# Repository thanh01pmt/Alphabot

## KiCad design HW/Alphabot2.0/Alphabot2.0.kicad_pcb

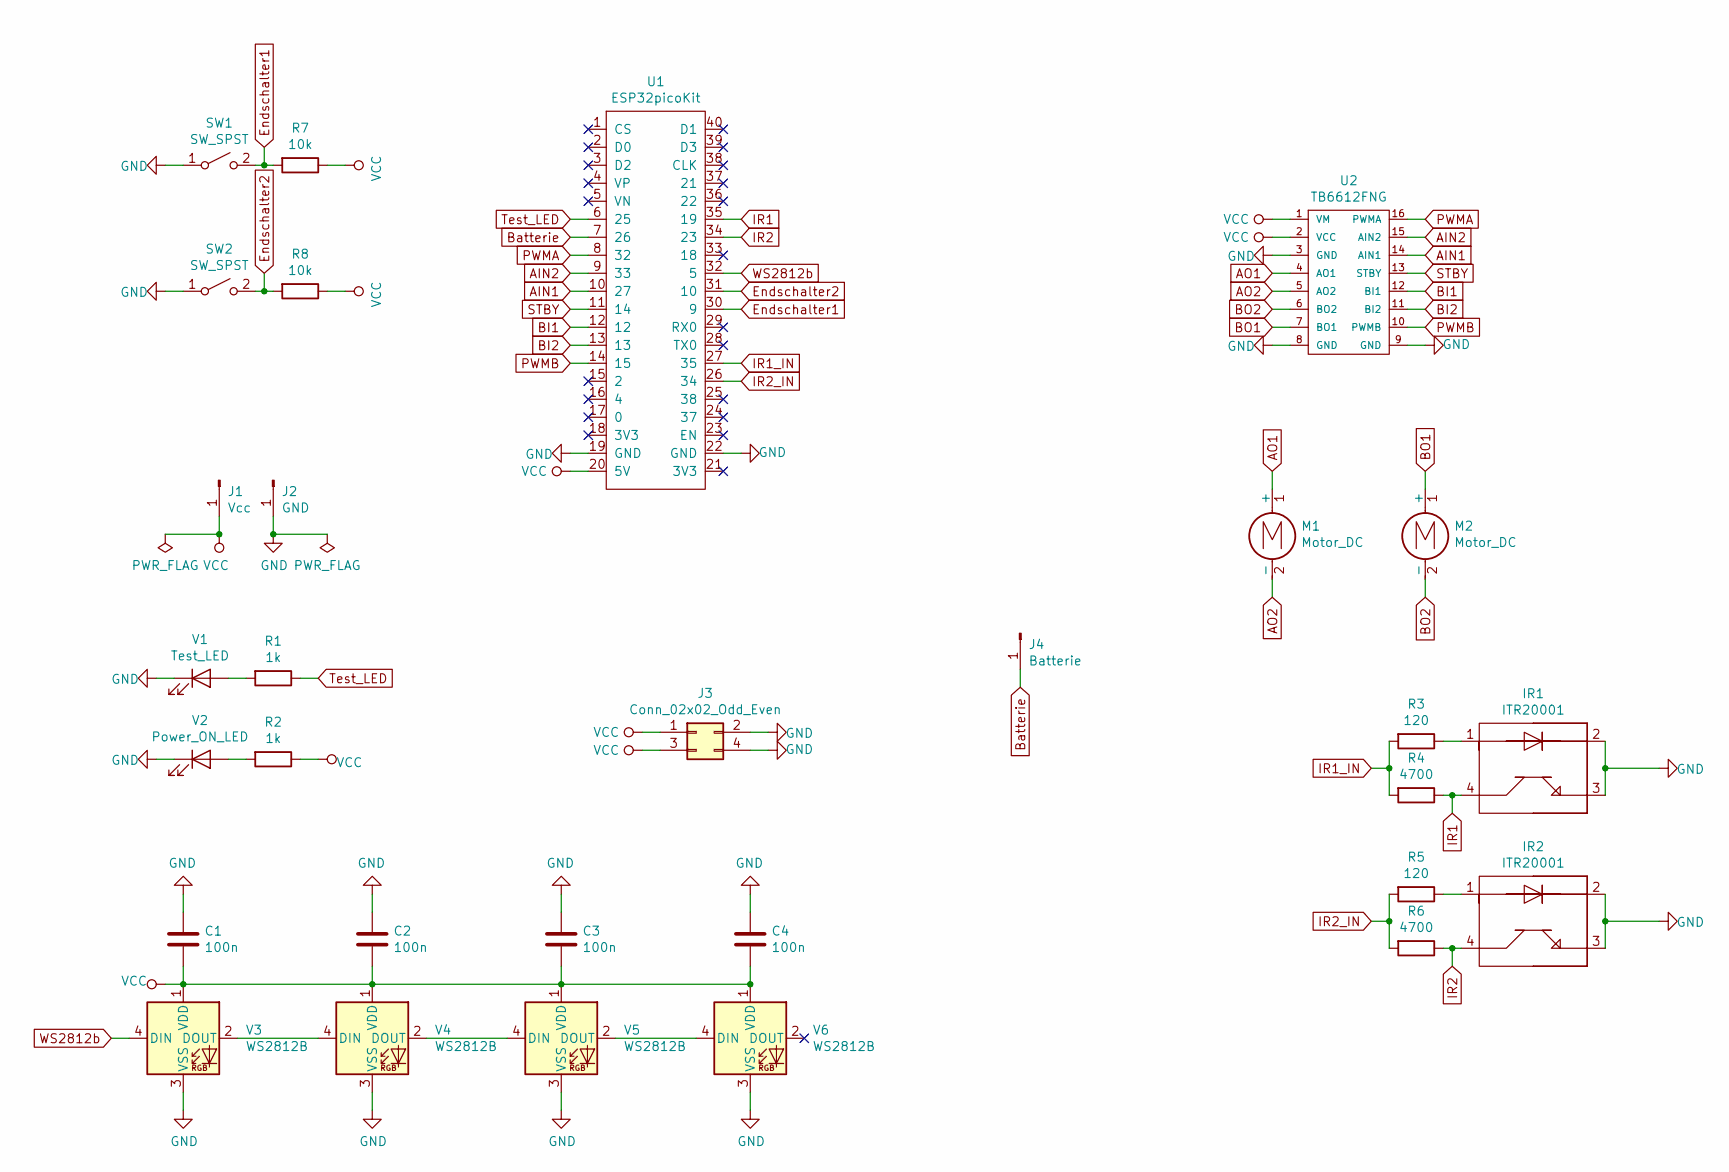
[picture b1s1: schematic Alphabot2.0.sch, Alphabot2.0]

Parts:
C1, C2, C3, C4: 100n; C_0805_2012Metric_Pad1.15x1.40mm_HandSolder
IR1, IR2: ITR20001; ITR20001-T
J1: Vcc; PinHeader_1x01_P2.54mm_Vertical
J2: GND; PinHeader_1x01_P2.54mm_Vertical
J3: Conn_02x02_Odd_Even; PinHeader_2x02_P2.54mm_Vertical_SMD
J4: Batterie; PinHeader_1x01_P2.54mm_Vertical
M1, M2: Motor_DC; N20_DC_Motor_mit_Halterung
R1, R2: 1k; R_0805_2012Metric_Pad1.15x1.40mm_HandSolder
R3, R5: 120; R_0805_2012Metric_Pad1.15x1.40mm_HandSolder
R4, R6: 4700; R_0805_2012Metric_Pad1.15x1.40mm_HandSolder
R7, R8: 10k; R_0805_2012Metric_Pad1.15x1.40mm_HandSolder
SW1, SW2: SW_SPST; Endschalter
U1: ESP32picoKit; ESP32_Pico_Kit
U2: TB6612FNG
V1: Test_LED; LED_0805_2012Metric_Pad1.15x1.40mm_HandSolder
V2: Power_ON_LED; LED_0805_2012Metric_Pad1.15x1.40mm_HandSolder
V3, V4, V5, V6: WS2812B; LED_WS2812B_PLCC4_5.0x5.0mm_P3.2mm

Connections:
AIN1: U1.10 (27), U2.14 (AIN1)
AIN2: U1.9 (33), U2.15 (AIN2)
AO1: M1.1 (+), U2.4 (AO1)
AO2: M1.2 (-), U2.5 (AO2)
BI1: U1.12, U2.12 (BI1)
BI2: U1.13, U2.11 (BI2)
BO1: M2.1 (+), U2.7 (BO1)
BO2: M2.2 (-), U2.6 (BO2)
Batterie: J4.1, U1.7 (26)
Endschalter1: R7.2, SW1.2 (B), U1.30 (9)
Endschalter2: R8.2, SW2.2 (B), U1.31 (10)
GND: C1.1, C2.1, C3.1, C4.1, IR1.2, IR1.3, IR2.2, IR2.3, J2.1, J3.2, J3.4, SW1.1 (A), SW2.1 (A), U1.19 (GND), U1.22 (GND), U2.3 (GND), U2.8 (GND), U2.9 (GND), V1.1 (K), V2.1 (K), V3.3 (VSS), V4.3 (VSS), V5.3 (VSS), V6.3 (VSS)
IR1: IR1.4, R4.1, U1.35 (19)
IR1_IN: R3.2, R4.2, U1.27 (35)
IR2: IR2.4, R6.1, U1.34 (23)
IR2_IN: R5.2, R6.2, U1.26 (34)
unnamed: IR1.1, R3.1
unnamed: IR2.1, R5.1
unnamed: R1.2, V1.2 (A)
unnamed: R2.2, V2.2 (A)
unnamed: V3.2 (DOUT), V4.4 (DIN)
unnamed: V4.2 (DOUT), V5.4 (DIN)
unnamed: V5.2 (DOUT), V6.4 (DIN)
PWMA: U1.8 (32), U2.16 (PWMA)
PWMB: U1.14 (15), U2.10 (PWMB)
STBY: U1.11 (14), U2.13 (STBY)
Test_LED: R1.1, U1.6 (25)
VCC: C1.2, C2.2, C3.2, C4.2, J1.1, J3.1, J3.3, R2.1, R7.1, R8.1, U1.20 (5V), U2.1 (VM), U2.2 (VCC), V3.1 (VDD), V4.1 (VDD), V5.1 (VDD), V6.1 (VDD)
WS2812b: U1.32 (5), V3.4 (DIN)

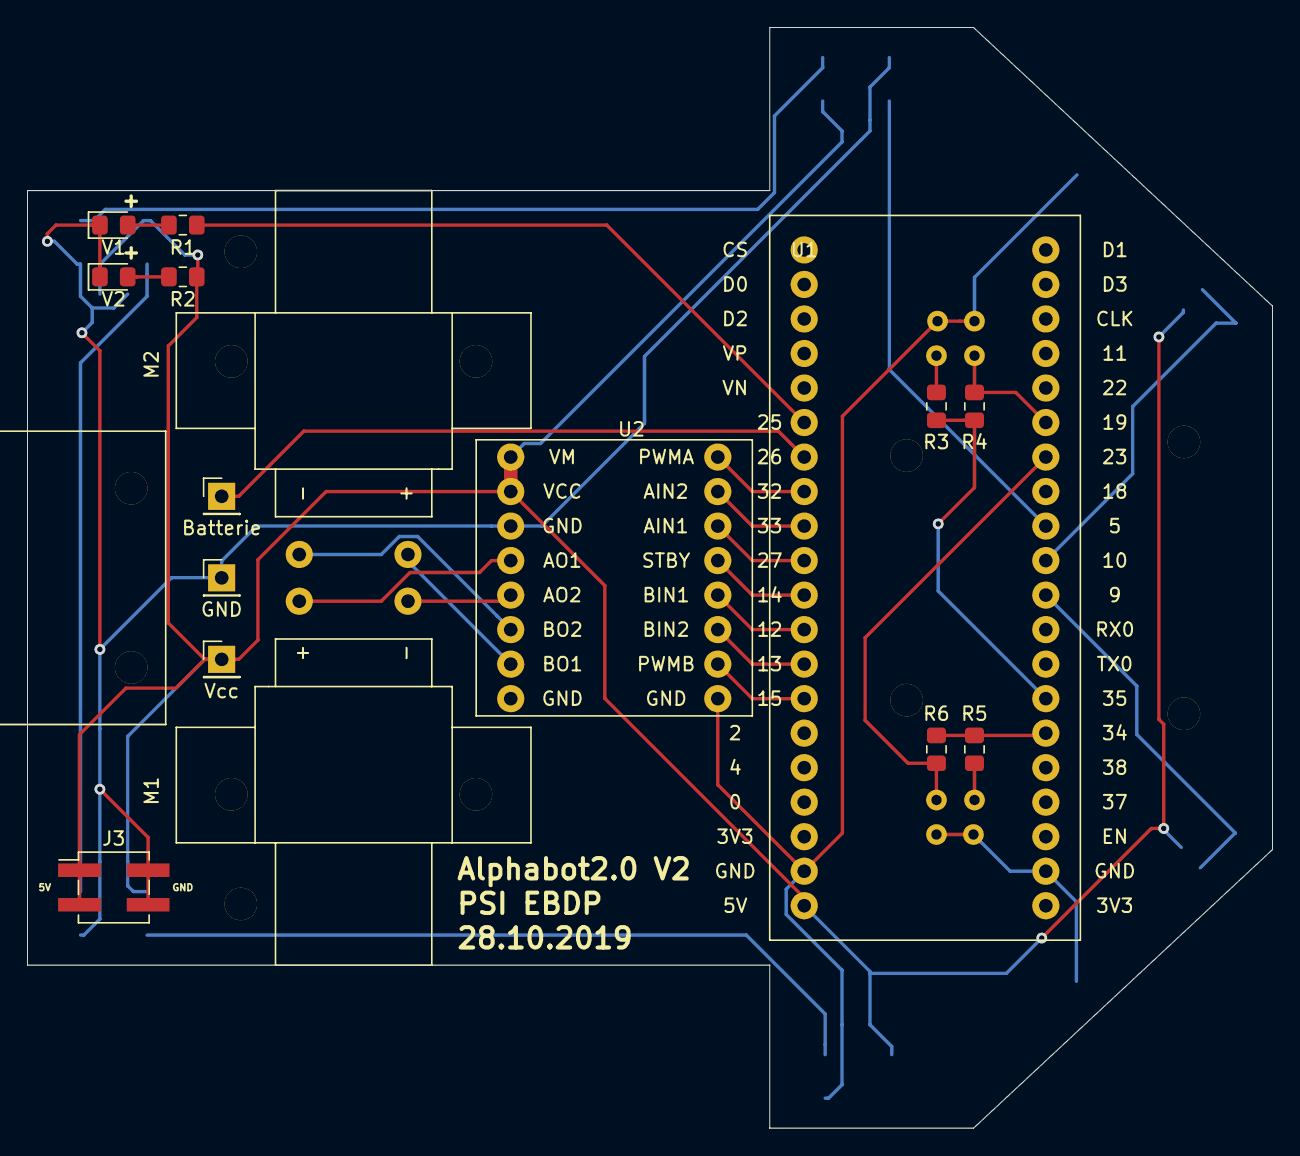
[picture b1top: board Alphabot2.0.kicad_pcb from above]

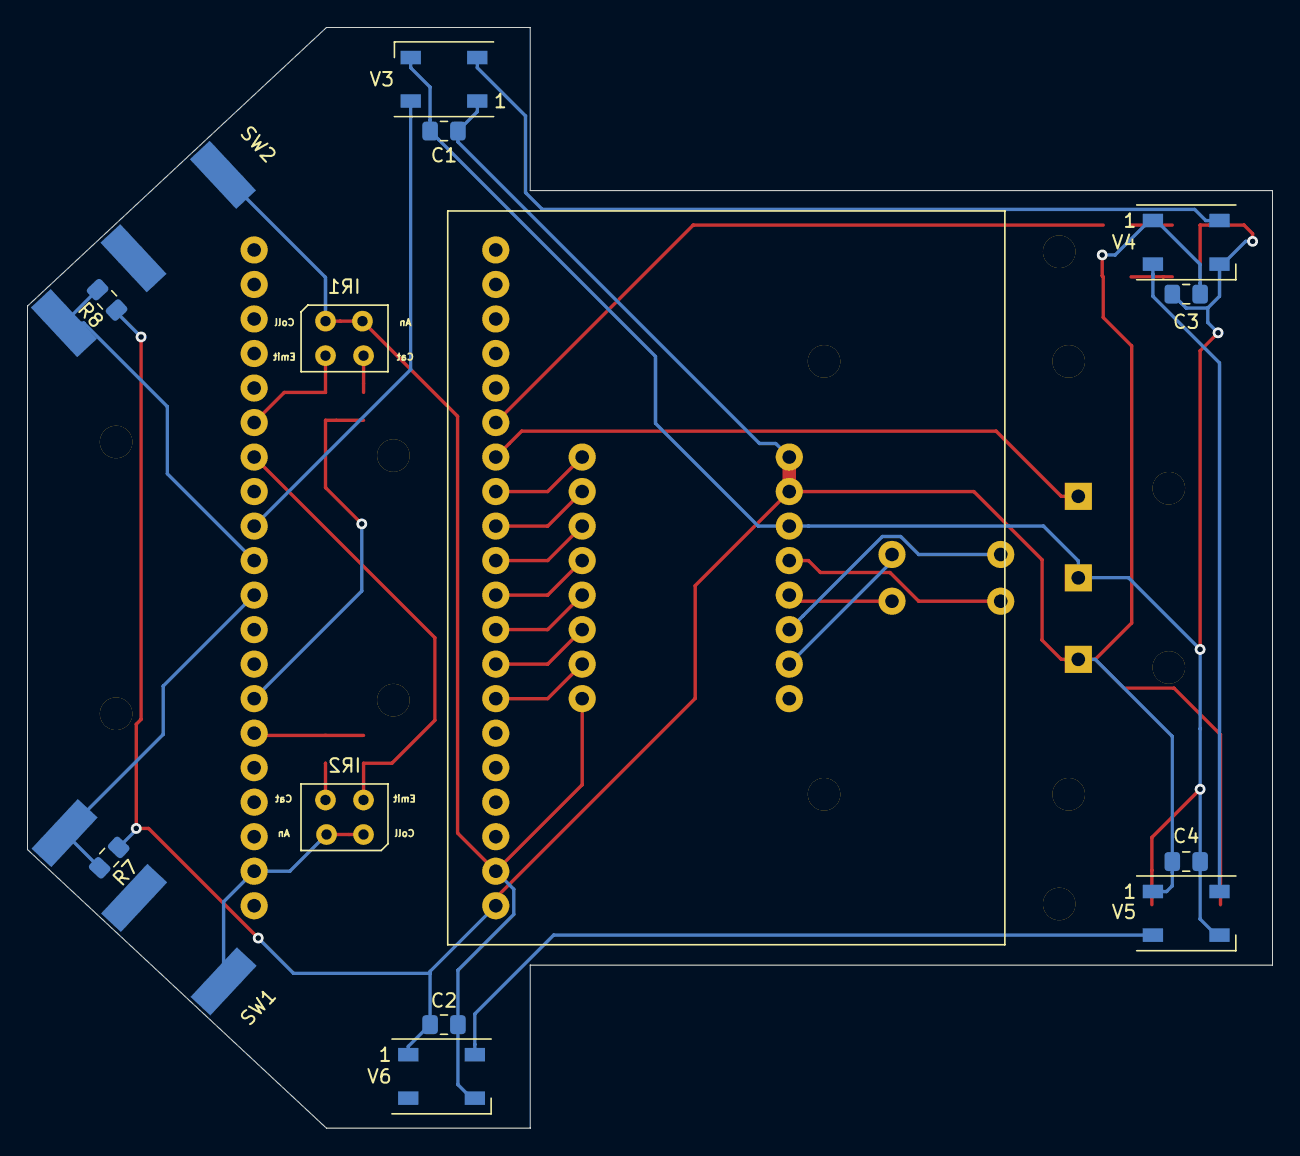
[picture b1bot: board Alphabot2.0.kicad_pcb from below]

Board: 2 copper layers, 91.6 x 81.0 mm, 30 parts (12 on the bottom side), 29 nets.

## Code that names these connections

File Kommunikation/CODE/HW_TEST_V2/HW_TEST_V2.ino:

#include <Adafruit_NeoPixel.h>
#ifdef __AVR__
 #include <avr/power.h>
#endif
#include <SparkFun_TB6612.h>

#define WS2812b  5
#define NUMPIXELS 4
#define AIN1 27
#define BIN1 12
#define AIN2 33
#define BIN2 13
#define PWMA 32
#define PWMB 15
#define STBY 14
#define IR_L_IN 22
#define IR_L_OUT 38
#define IR_R_IN 18
#define IR_R_OUT 37
#define END_R 9
#define END_L 10
#define TEST_LED 25

bool test_led_bup = false;
char r = 0;
char g = 0;
char b = 128;
const int offsetA = -1;
const int offsetB = 1;
int zahl = 0;

Motor motorR = Motor(AIN1, AIN2, PWMA, offsetA, STBY, 0);
Motor motorL = Motor(BIN1, BIN2, PWMB, offsetB, STBY, 1);

// LED
Adafruit_NeoPixel pixels(NUMPIXELS, WS2812b, NEO_GRB + NEO_KHZ800);
void setup() {

  Serial.begin(9600);
  pinMode(TEST_LED, OUTPUT);
  pinMode(IR_L_OUT, INPUT);
  pinMode(IR_R_OUT, INPUT);
  pinMode(END_R, INPUT);
  pinMode(END_L, INPUT);
  pinMode(IR_L_IN, OUTPUT);
  pinMode(IR_R_IN, OUTPUT);
  
   for(int i=0; i<NUMPIXELS; i++) { // For each pixel...
    pixels.setPixelColor(i, pixels.Color(r, g, b));
    pixels.show();   // Send the updated pixel colors to the hardware.
  }

  digitalWrite(IR_R_IN, HIGH);
  digitalWrite(IR_L_IN, HIGH);
  // LED
  pixels.begin(); // INITIALIZE NeoPixel strip object (REQUIRED)

   for(int i=0; i<NUMPIXELS; i++) { // For each pixel...
    pixels.setPixelColor(i, pixels.Color(255, 255, 255));
    pixels.show();   // Send the updated pixel colors to the hardware.
    delay(500);
  }
  
}

void loop() {
  
  motorL.drive(255,0);
  motorR.drive(255,0);

  for(r = 0; r < 128; r++){
    b--;
    for(int i = 0; i < 4; i++){
      pixels.setPixelColor(i, pixels.Color(r, g, b));
      pixels.show();   // Send the updated pixel colors to the hardware.
    }
    delay(10);
    
  }
  for(g = 0; g < 128; g++){
    r--;
    for(int i = 0; i < 4; i++){
      pixels.setPixelColor(i, pixels.Color(r, g, b));
      pixels.show();   // Send the updated pixel colors to the hardware.
    }
    delay(10);
  }
  for(b = 0; b < 128; b++){
    g--;
    for(int i = 0; i < 4; i++){
      pixels.setPixelColor(i, pixels.Color(r, g, b));
      pixels.show();   // Send the updated pixel colors to the hardware.
    }
    delay(10);
  }


  if(test_led_bup == false){
    test_led_bup = true;
    digitalWrite(TEST_LED, HIGH);
  }
  else{
    test_led_bup = false;
    digitalWrite(TEST_LED, LOW);
  }
  
  delay(10);
}
